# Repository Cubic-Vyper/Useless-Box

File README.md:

# Useless-Box
This is a useless box that only stays when a secret button is held.
I'm making this because I thought it would be a great challange.

Stasis Page PDF (cuz you would need an account to view the page): https://github.com/Cubic-Vyper/Useless-Box/blob/a6bbfdbe64c2ba0163d5f215921f39e9bf6420dd/Stasis_ProjectPage-Useless%20Box.pdf

--------------
**Bill Of Materials**

| Name | Purpose | Cost Per Item (USD) | Quantity | Total (USD) | Link | Distributor |
|------|---------|---------------------|----------|-------------|------|--------------|
| M3 10mm bolts | This will hold it together | 3.29 | 4 | 3.29 | [Link to Listing](https://www.aliexpress.us/item/3256801599375629.html) | Aliexpress |
| Copper Foil Tape | I will use this to make my own PCB | 7.79 | 1 | 7.79 | [Link to Listing](https://www.aliexpress.us/item/3256807024977285.html) | Aliexpress |
| Limit Switch | This will tell the servo when it is in the bottom position | 1.79 | 1 | 1.79 | [Link to Listing](https://www.aliexpress.us/item/2251832626205701.html) | Aliexpress |
| SG90 Servo | This will flip the main switch | 2.79 | 1 | 2.79 | [Link to Listing](https://www.aliexpress.us/item/3256810609060502.html) | Aliexpress |
| RP2040-Zero | this will control everything | 2.39 | 1 | 2.39 | [Link to Listing](https://www.aliexpress.us/item/3256806674577118.html) | Aliexpress |
| Toggle Switch | This is the main switch | 3.19 | 1 | 3.19 | [Link to Listing](https://www.aliexpress.us/item/3256810165691713.html) | Aliexpress |
| ttp223 capacitive touch sensor | This is the secret switch that will keep the main switch flipped | 1.39 | 1 | 1.39 | [Link to Listing](https://www.aliexpress.us/item/3256807294486410.html) | Aliexpress |
| 3D Printed Case | This will hold everything | 0.00 | 1 | 0.00 | There isn't a link | I will print this |

------------------------

---------------------

**assembly**

first screw or glue the parts to the base

screw the arm on

now screw the walls on

and glue the touch sensor here (or anywhere you want)

add the hinged door with some filiment, insert fillement into the hinge

glue the lid on

and add the toggle switch ussing the nut that comes with it

now it's done!

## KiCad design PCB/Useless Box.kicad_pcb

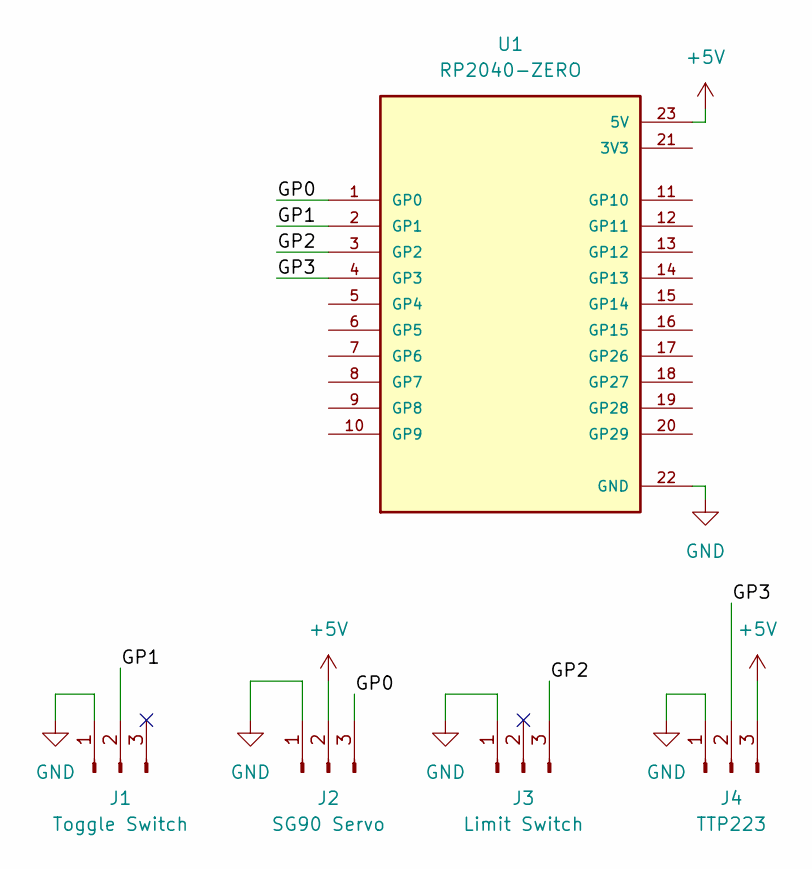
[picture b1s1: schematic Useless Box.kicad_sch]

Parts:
J1: Toggle Switch; PinHeader_1x03_P2.54mm_Vertical
J2: SG90 Servo; PinHeader_1x03_P2.54mm_Vertical
J3: Limit Switch; PinHeader_1x03_P2.54mm_Vertical
J4: TTP223; PinHeader_1x03_P2.54mm_Vertical
U1: RP2040-ZERO; MODULE_RP2040-ZERO; PARTREV NA

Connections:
+5V: J2.2, J4.3, U1.23 (5V)
/GP0: J2.3, U1.1 (GP0)
/GP1: J1.2, U1.2 (GP1)
/GP2: J3.3, U1.3 (GP2)
/GP3: J4.2, U1.4 (GP3)
GND: J1.1, J2.1, J3.1, J4.1, U1.22 (GND)

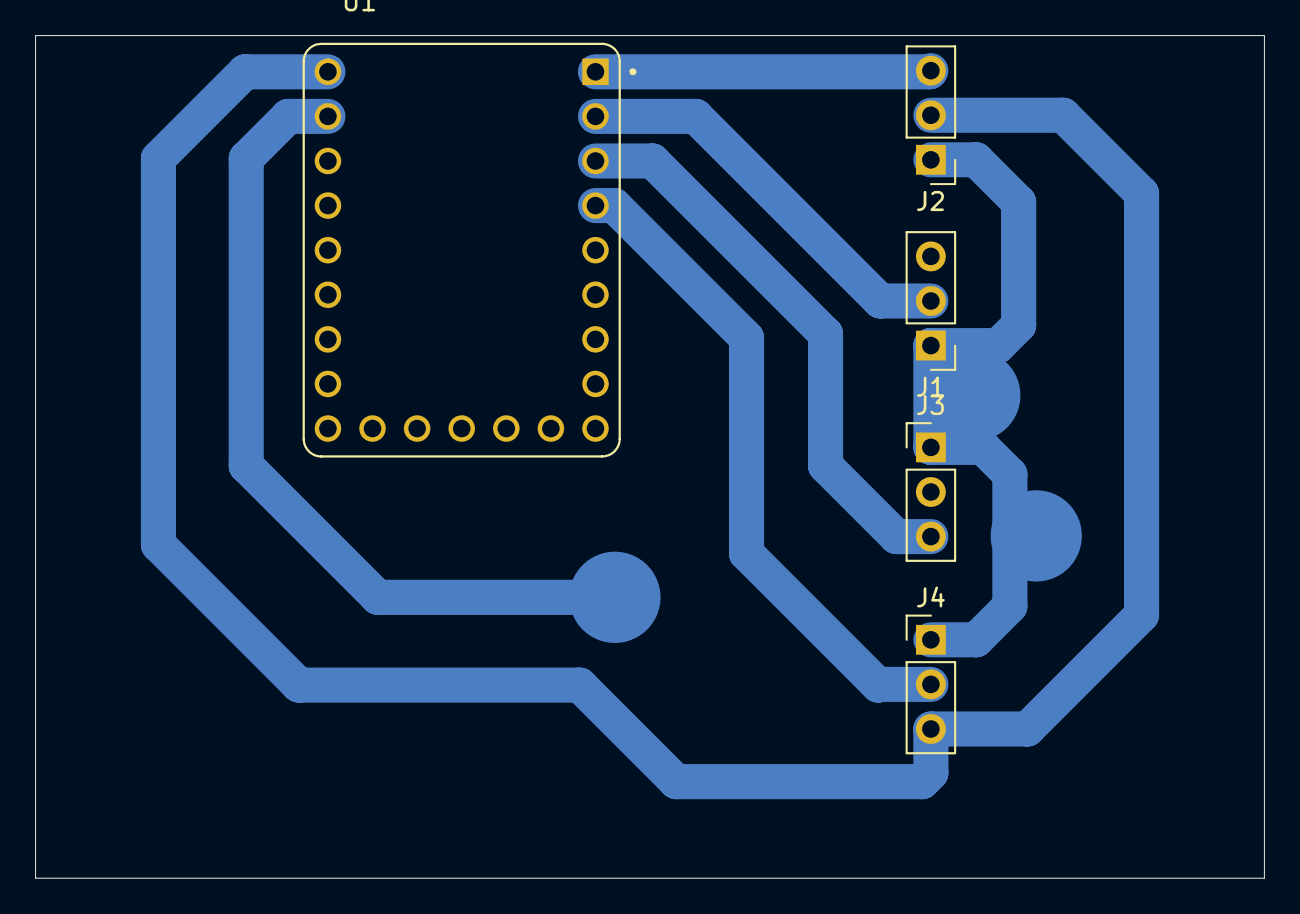
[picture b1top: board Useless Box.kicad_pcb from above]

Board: 2 copper layers, 70.0 x 48.0 mm, 5 parts (0 on the bottom side), 6 nets.

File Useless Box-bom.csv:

Name,Purpose,Quantity,Total Cost (USD),Link,Distributor
"M3 10mm bolts","This will hold it together",4,3.29,"https://www.aliexpress.us/item/3256801599375629.html","Aliexpress"
"Copper Foil Tape","I will use this to make my own PCB",1,7.79,"https://www.aliexpress.us/item/3256807024977285.html","Aliexpress"
"Limit Switch","This will tell the servo when it is in the bottom position",1,1.79,"https://www.aliexpress.us/item/2251832626205701.html","Aliexpress"
"SG90 Servo","This will flip the main switch",1,2.79,"https://www.aliexpress.us/item/3256810609060502.html","Aliexpress"
"RP2040-Zero","this will control everything",1,2.39,"https://www.aliexpress.us/item/3256806674577118.html","Aliexpress"
"Toggle Switch","This is the main switch",1,3.19,"https://www.aliexpress.us/item/3256810165691713.html","Aliexpress"
"ttp223 capacitive touch sensor","This is the secret switch that will keep the main switch flipped",1,1.39,"https://www.aliexpress.us/item/3256807294486410.html","Aliexpress"
"3D Printed Case","This will hold everything",$0.00,1,$0.00,"There isn't a link","I will print this"
